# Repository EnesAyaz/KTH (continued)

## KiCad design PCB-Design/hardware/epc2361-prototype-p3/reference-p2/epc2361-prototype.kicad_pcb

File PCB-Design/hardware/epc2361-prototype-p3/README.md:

# P3 — left-side DC input and gate driver

This revision supersedes P2 for placement review. It is not released for manufacturing.

## Implemented arrangement

85 × 55 mm, four layers. DC+ and DC− M4 terminals are on the upper left, with auxiliary power and HI/LI inputs on the left edge. AC is on the right. LMG1210 is immediately left of the switch group. Both switch pairs face left toward the driver. There are two EPC2361s per switch, four total.

Twenty-four TDK C2012X7S2A105K125AB bus capacitors are fitted: six above and six below each local half bridge. All are on the top face. Upper banks C1–C6 and C19–C24 directly serve the short local commutation paths; lower banks C7–C12 and C25–C30 supplement DC-link decoupling through the collectors. The count was increased so the lower row does not require a long top-layer positive feeder to the high-side devices. Nominal total is 24 µF; effective capacitance at 75 V and permissible RMS ripple have not been established.

Every component has a silkscreen reference. Gate/source headers are marked G and S; the control header has individual 12V/GND/HI/GND/LI/GND labels. DC and AC terminals and all five test points are identified. The BOM contains all 51 purchased components; five additional footprints are copper test points.

## Four-layer allocation

| Layer | Actual baseline P3 use |
|---|---|
| L1 / F.Cu | Components, local DC+/AC/DC− power islands, local gate escapes and decoupling |
| L2 / In1.Cu | Continuous DC− plane underneath the power cells; no routed signals |
| L3 / In2.Cu | DC+ collector, with auxiliary/control and source-return routes |
| L4 / B.Cu | AC collector and gate-drive routes |

L1 is not a whole-board DC+ plane. The commutation current passes through separate positive, switch-node and negative regions. L2 provides a nearby opposing current path. L3/L4 are already used for power distribution as well as driver connections; they are not two unused signal layers.

The gate-routing candidate adds explicit star branches and source-return corridors on the lower layers. Consult its separate report for its actual result before adopting it. A gate route over an unrelated DC+ plane is not automatically a properly referenced gate loop.

## Proposed stackup for fabricator review

F.Cu 0.070 mm / dielectric 0.100 mm / In1.Cu 0.035 mm / core 1.190 mm / In2.Cu 0.035 mm / dielectric 0.100 mm / B.Cu 0.070 mm. Copper plus dielectric totals 1.600 mm, excluding masks. The 0.100 mm outer dielectric spacing is a requested finished value, not a confirmed catalogue stackup. Manufacturer tolerances and 0.15 mm routing at the chosen finished copper weight must be accepted before ordering. Finish and assembly stencil remain unspecified.

## Inductance interpretation

Both primary upper-bank local geometries now share the same 6 mm device spacing and 0.100 mm top-to-return dielectric. The P2 selected external finger estimate (~0.385 nH) and six-capacitor ideal component ESL (~0.080 nH) apply only to those selected local contributions. Their ~0.47 nH subtotal is not the complete loop or a measured value. Lower-bank vias, shared collectors, package contributions and coupling require extraction; do not divide component ESL by all 24 capacitors and call that the switching-loop ESL.

## Electrical and mechanical release items

Design targets remain 75 V maximum, 36.7 A RMS / 51.9 A peak total output, 50 kHz nominal and 100 kHz maximum. Current capability and thermal rise have not been validated. The gate-routing report must demonstrate acceptable branch symmetry and source-return topology; DRC alone cannot do this. Current distribution through collectors and vias, MLCC bias/ripple, bootstrap operating range and actual gate overshoot also remain engineering checks.

The controller supplies nonoverlapping HI/LI in independent-input mode; bootstrap startup/refresh is required. JCTRL1 is not isolated. Gate headers must not be driven by a second active driver while onboard outputs are connected. Individual 0 Ω gate-resistor footprints remain for tuning and isolation.

Cold plate, insulating TIM, clamping force, mechanical mounting and cable-lug support are not designed. Tall headers and capacitors constrain the plate underside. No fabrication-ready claim is made while these remain open. Exact EPC2361 and LMG1210 manufacturer models are still unavailable: their local 3D models are explicitly approximate envelopes. Generic header and capacitor models require manufacturer-dimension comparison.

## Project files

Open epc2361-prototype-p3.kicad_pro; open its PCB and press Alt+3 for 3D. BOM.md / BOM.json are the revised component lists. The schematic and PCB use local footprints and local visualization models. connectivity-check.txt checks exported net assignments and model presence; drc.rpt records baseline geometric checks. A separate gate candidate is not the baseline released design. P2 files copied into this folder during preparation are historical; use only the P3-named project for this revision.

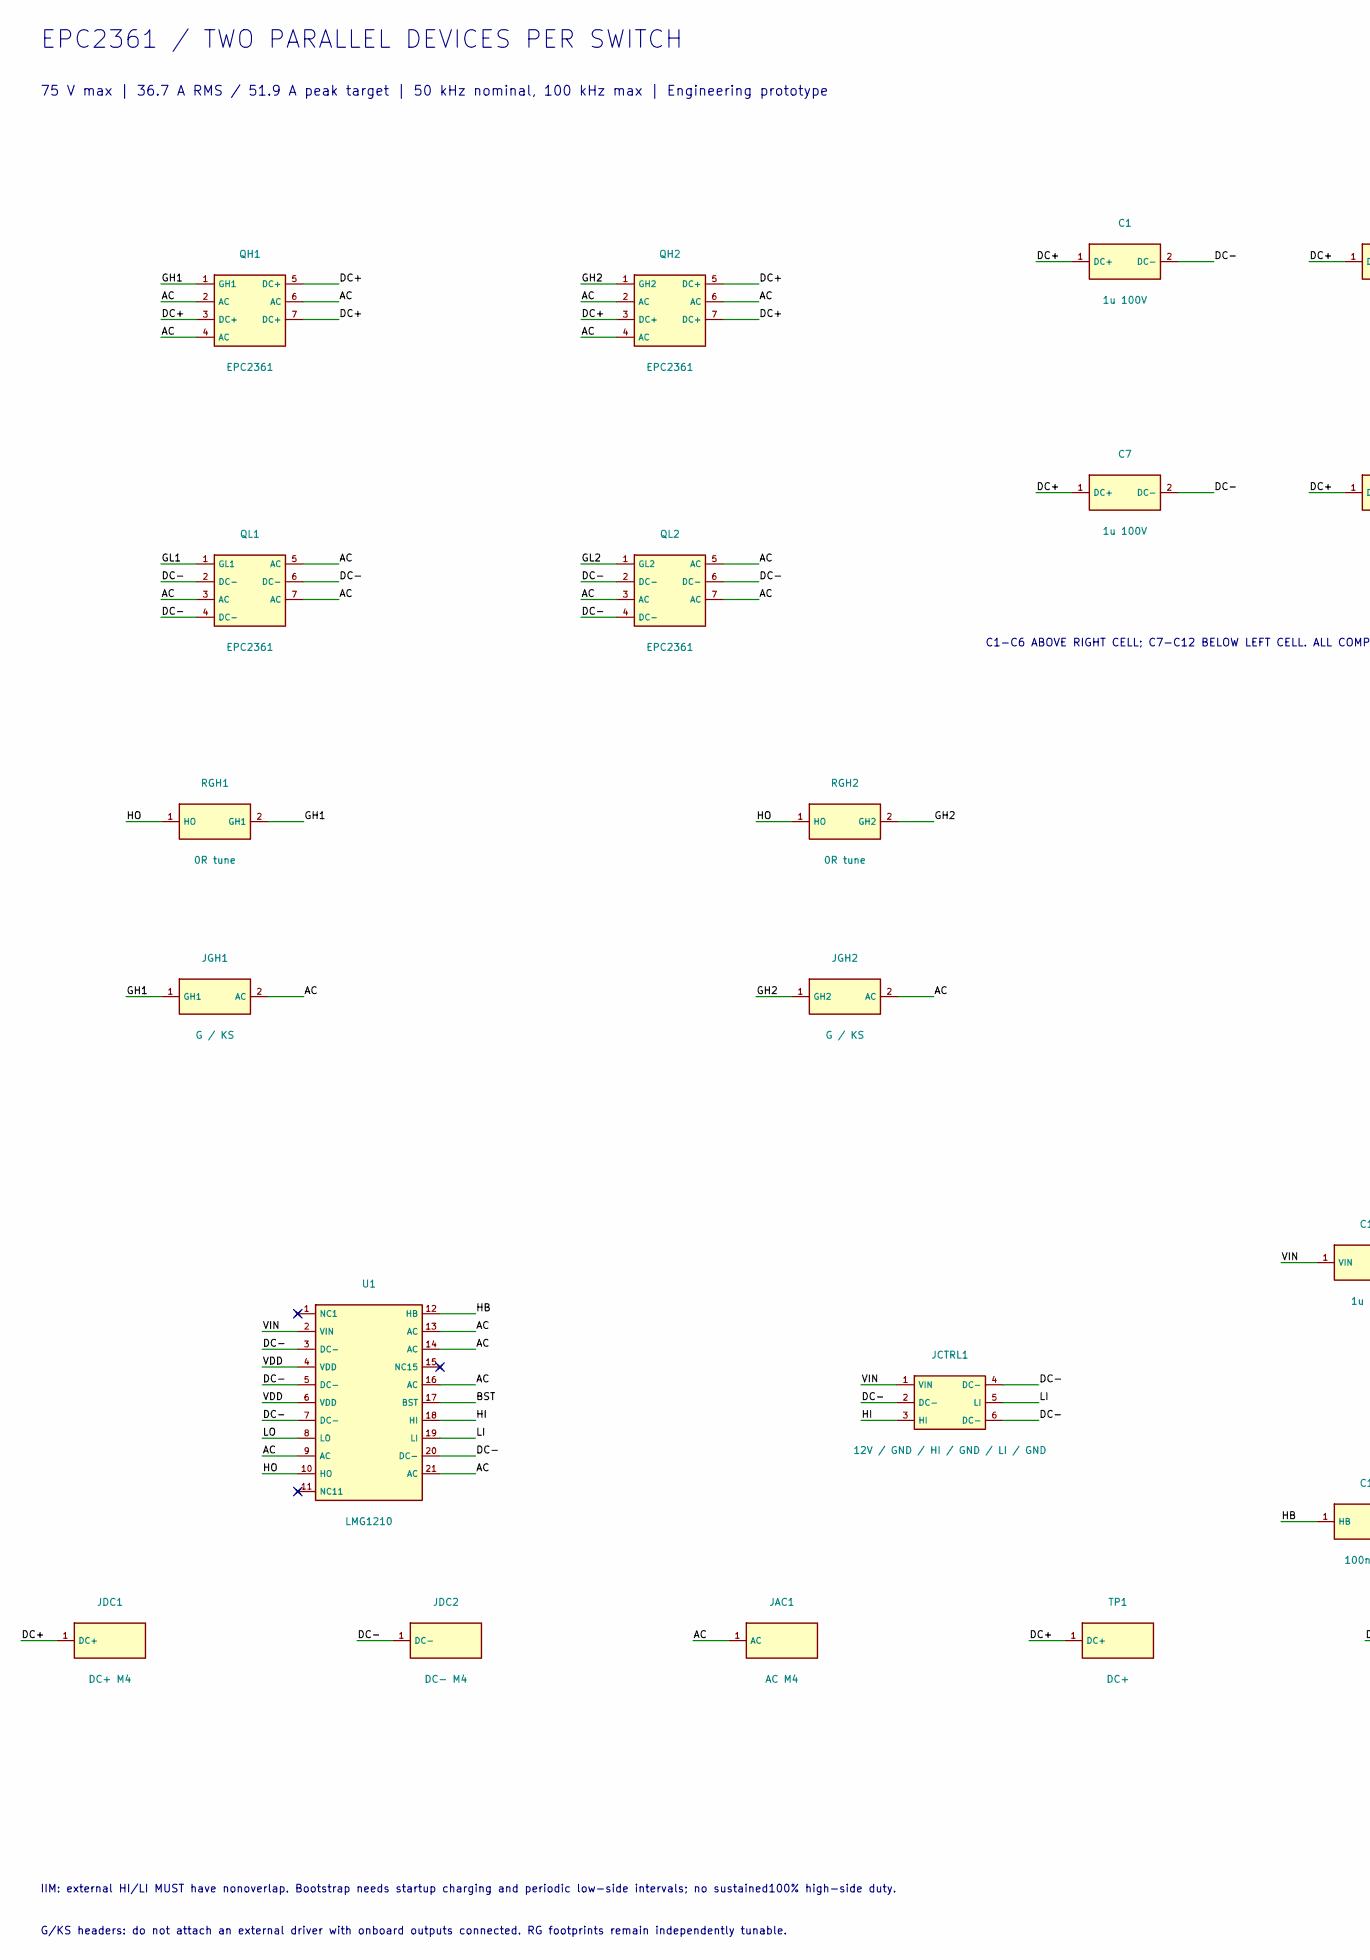
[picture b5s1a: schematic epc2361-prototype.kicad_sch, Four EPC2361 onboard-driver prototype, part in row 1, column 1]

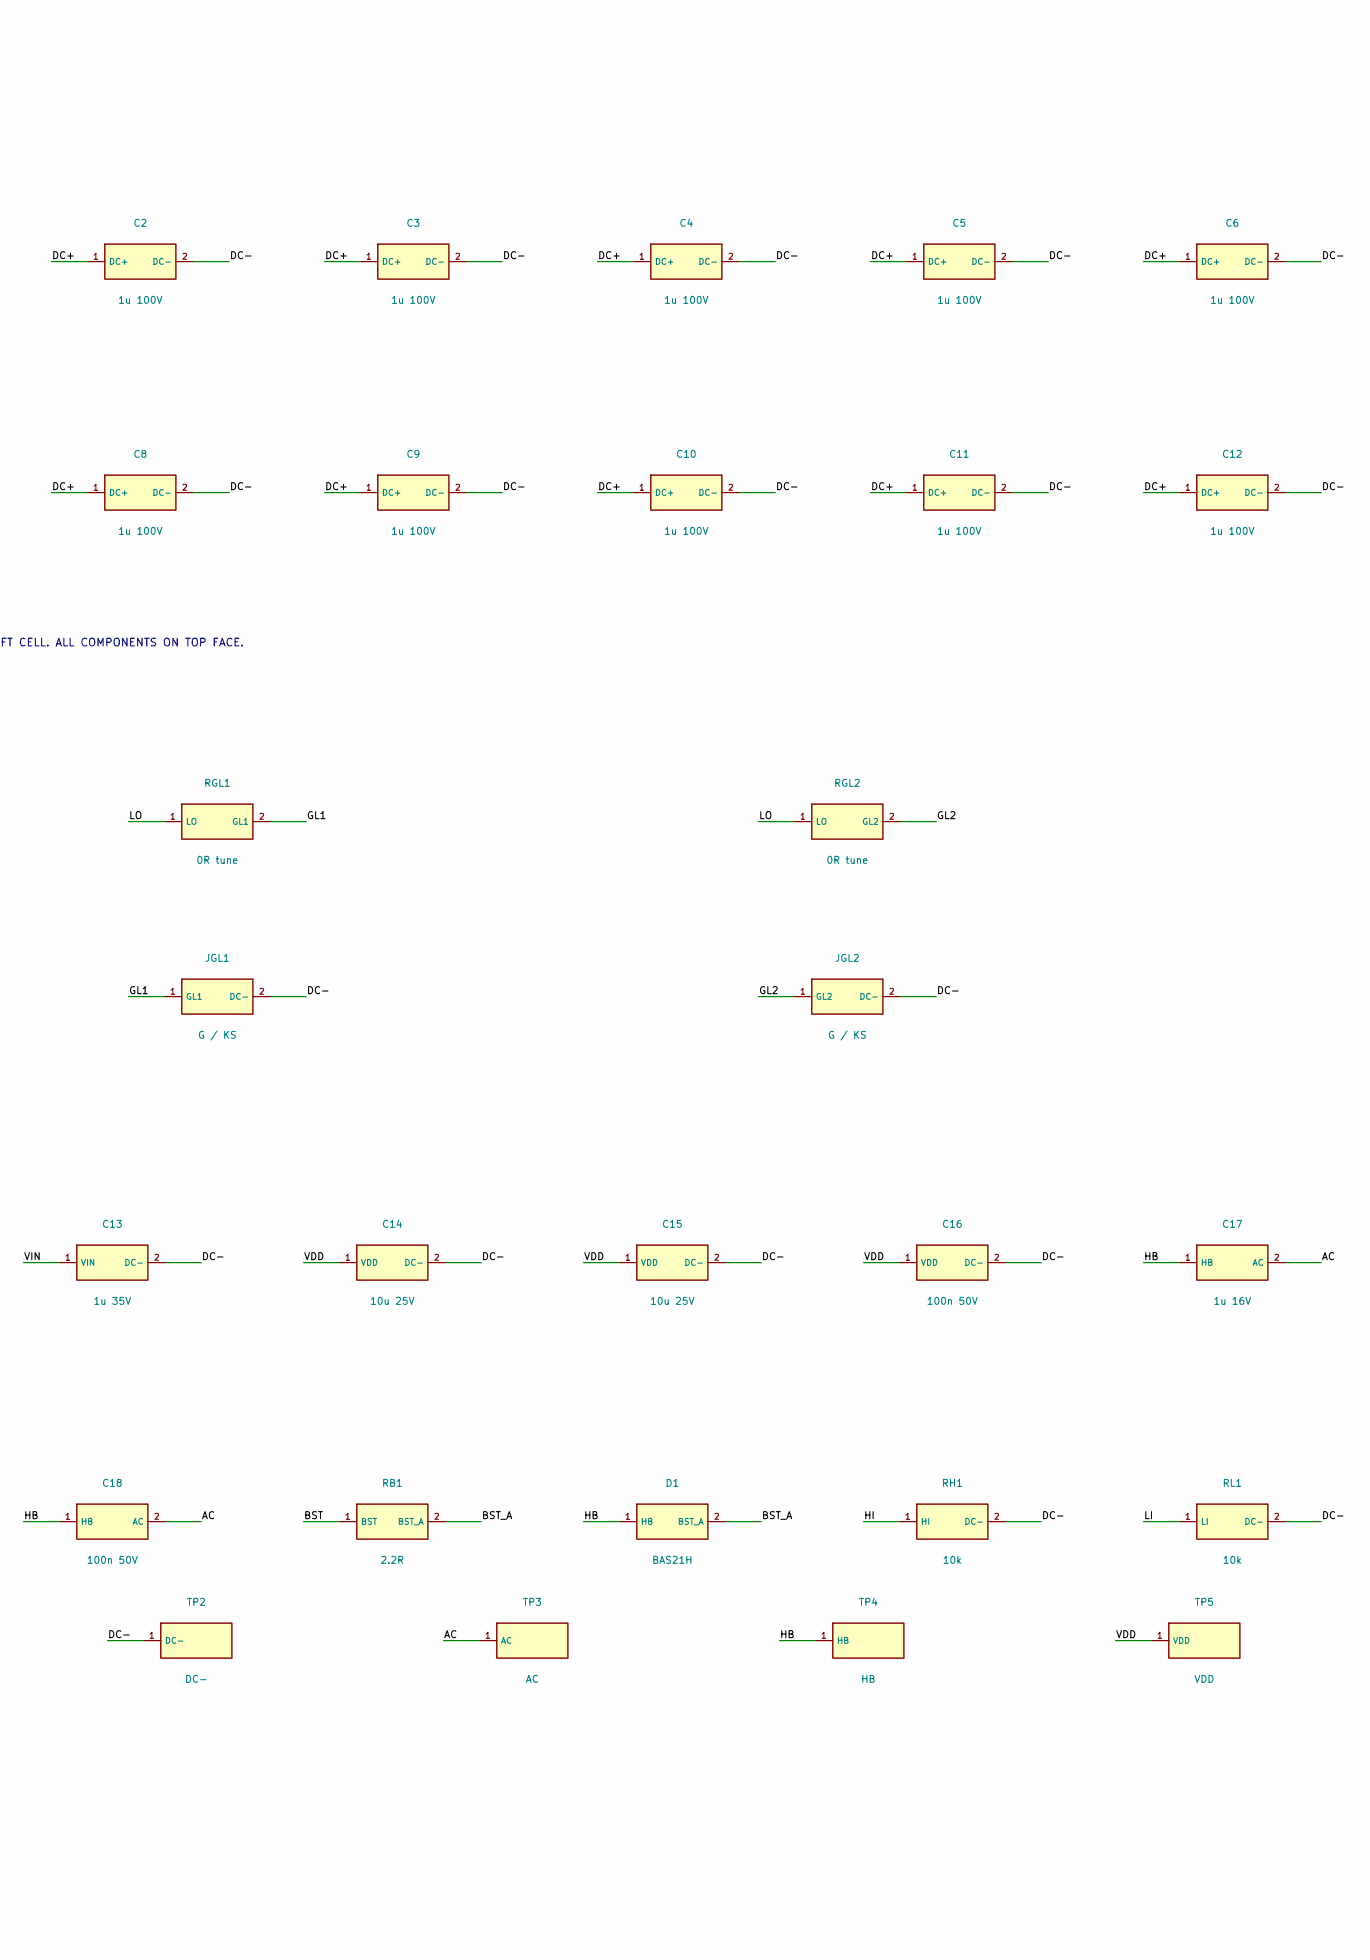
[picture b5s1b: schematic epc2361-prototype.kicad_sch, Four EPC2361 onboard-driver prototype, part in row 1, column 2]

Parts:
C1, C2, C3, C4, C5, C6, C7, C8, C9, C10, C11, C12: 1u 100V; C_0805_2012Metric
C13: 1u 35V; C_0603_1608Metric
C14, C15: 10u 25V; C_0805_2012Metric
C16, C18: 100n 50V; C_0603_1608Metric
C17: 1u 16V; C_0603_1608Metric
D1: BAS21H; D_SOD-123F
JAC1: AC M4; Wuerth_REDCUBE-THR_WP-THRBU_74650094_THR
JCTRL1: 12V / GND / HI / GND / LI / GND; PinHeader_1x06_P2.54mm_Vertical
JDC1: DC+ M4; Wuerth_REDCUBE-THR_WP-THRBU_74650094_THR
JDC2: DC- M4; Wuerth_REDCUBE-THR_WP-THRBU_74650094_THR
JGH1, JGH2: G / KS; PinHeader_1x02_P1.27mm_Vertical
JGL1, JGL2: G / KS; PinHeader_1x02_P1.27mm_Vertical
QH1, QH2: EPC2361
QL1, QL2: EPC2361
RB1: 2.2R; R_0603_1608Metric
RGH1, RGH2: 0R tune; R_0402_1005Metric
RGL1, RGL2: 0R tune; R_0402_1005Metric
RH1: 10k; R_0402_1005Metric
RL1: 10k; R_0402_1005Metric
TP1: DC+; Probe_Pad
TP2: DC-; Probe_Pad
TP3: AC; Probe_Pad
TP4: HB; Probe_Pad
TP5: VDD; Probe_Pad
U1: LMG1210; LMG1210_RVR

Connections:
AC: C17.2 (AC), C18.2 (AC), JAC1.1, JGH1.2 (AC), JGH2.2 (AC), QH1.2 (AC), QH1.4 (AC), QH1.6 (AC), QH2.2 (AC), QH2.4 (AC), QH2.6 (AC), QL1.3 (AC), QL1.5 (AC), QL1.7 (AC), QL2.3 (AC), QL2.5 (AC), QL2.7 (AC), TP3.1, U1.9 (AC), U1.13 (AC), U1.14 (AC), U1.16 (AC), U1.21 (AC)
BST: RB1.1 (BST), U1.17 (BST)
BST_A: D1.2 (BST_A), RB1.2 (BST_A)
DC+: C1.1 (DC+), C2.1 (DC+), C3.1 (DC+), C4.1 (DC+), C5.1 (DC+), C6.1 (DC+), C7.1 (DC+), C8.1 (DC+), C9.1 (DC+), C10.1 (DC+), C11.1 (DC+), C12.1 (DC+), JDC1.1, QH1.3 (DC+), QH1.5 (DC+), QH1.7 (DC+), QH2.3 (DC+), QH2.5 (DC+), QH2.7 (DC+), TP1.1
DC-: C1.2 (DC-), C2.2 (DC-), C3.2 (DC-), C4.2 (DC-), C5.2 (DC-), C6.2 (DC-), C7.2 (DC-), C8.2 (DC-), C9.2 (DC-), C10.2 (DC-), C11.2 (DC-), C12.2 (DC-), C13.2 (DC-), C14.2 (DC-), C15.2 (DC-), C16.2 (DC-), JCTRL1.2 (DC-), JCTRL1.4 (DC-), JCTRL1.6 (DC-), JDC2.1, JGL1.2 (DC-), JGL2.2 (DC-), QL1.2 (DC-), QL1.4 (DC-), QL1.6 (DC-), QL2.2 (DC-), QL2.4 (DC-), QL2.6 (DC-), RH1.2 (DC-), RL1.2 (DC-), TP2.1, U1.3 (DC-), U1.5 (DC-), U1.7 (DC-), U1.20 (DC-)
GH1: JGH1.1 (GH1), QH1.1 (GH1), RGH1.2 (GH1)
GH2: JGH2.1 (GH2), QH2.1 (GH2), RGH2.2 (GH2)
GL1: JGL1.1 (GL1), QL1.1 (GL1), RGL1.2 (GL1)
GL2: JGL2.1 (GL2), QL2.1 (GL2), RGL2.2 (GL2)
HB: C17.1 (HB), C18.1 (HB), D1.1 (HB), TP4.1, U1.12 (HB)
HI: JCTRL1.3 (HI), RH1.1 (HI), U1.18 (HI)
HO: RGH1.1 (HO), RGH2.1 (HO), U1.10 (HO)
LI: JCTRL1.5 (LI), RL1.1 (LI), U1.19 (LI)
LO: RGL1.1 (LO), RGL2.1 (LO), U1.8 (LO)
NC1: U1.1 (NC1)
NC11: U1.11 (NC11)
NC15: U1.15 (NC15)
VDD: C14.1 (VDD), C15.1 (VDD), C16.1 (VDD), TP5.1, U1.4 (VDD), U1.6 (VDD)
VIN: C13.1 (VIN), JCTRL1.1 (VIN), U1.2 (VIN)

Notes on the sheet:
EPC2361 / TWO PARALLEL DEVICES PER SWITCH
75 V max | 36.7 A RMS / 51.9 A peak target | 50 kHz nominal, 100 kHz max | Engineering prototype
C1-C6 ABOVE RIGHT CELL; C7-C12 BELOW LEFT CELL. ALL COMPONENTS ON TOP FACE.
IIM: external HI/LI MUST have nonoverlap. Bootstrap needs startup charging and periodic low-side intervals; no sustained100% high-side duty.
G/KS headers: do not attach an external driver with onboard outputs connected. RG footprints remain independently tunable.

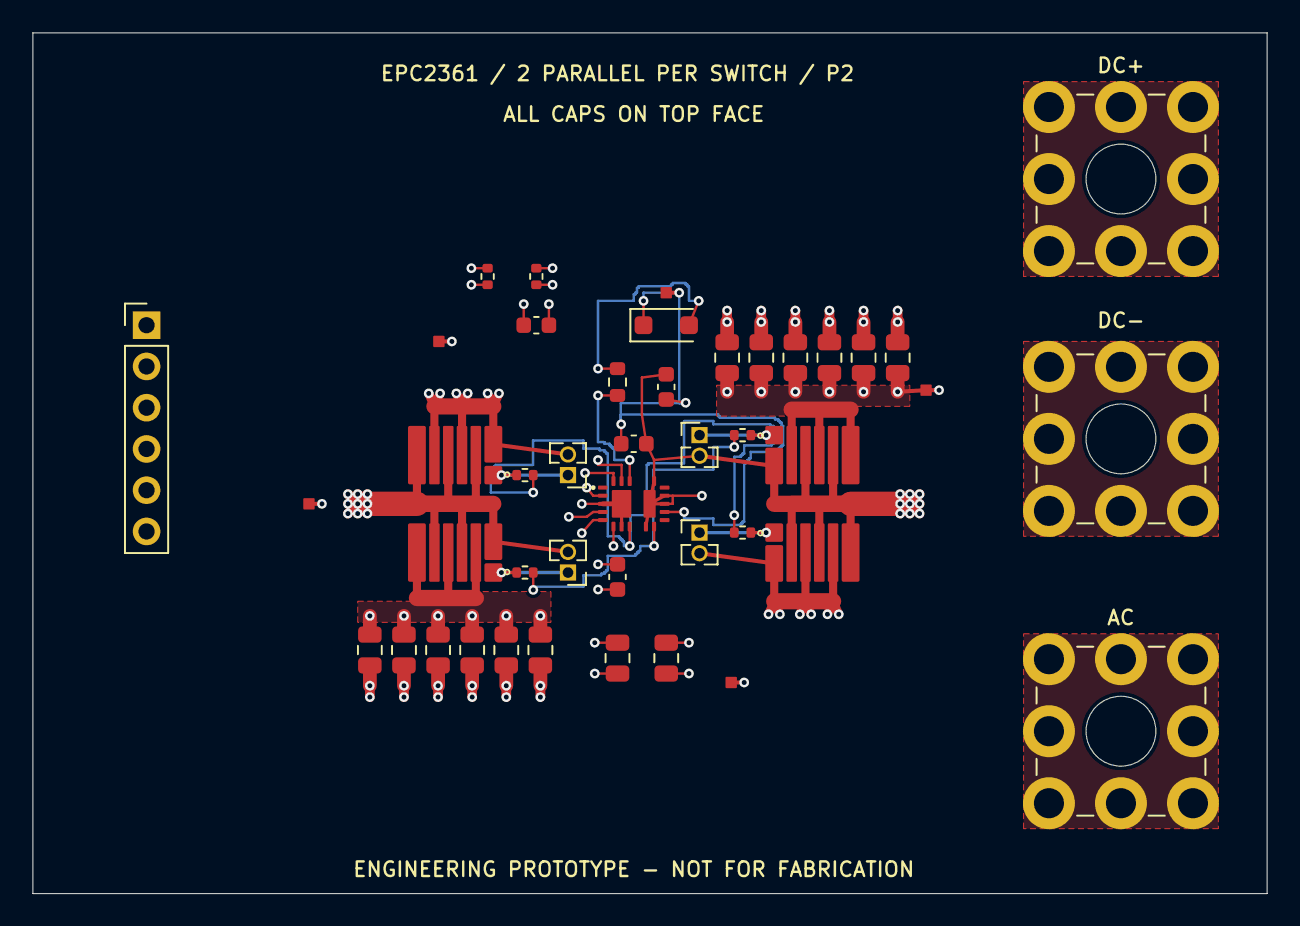
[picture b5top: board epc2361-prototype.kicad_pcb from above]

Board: 4 copper layers, 76.0 x 53.0 mm, 44 parts (0 on the bottom side), 16 nets.

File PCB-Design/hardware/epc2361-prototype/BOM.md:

# Prototype BOM

All quantities are for one four-FET board. Provisional engineering BOM; not purchasing release.

| References | Qty | MPN | Value | Footprint | Fit | Notes |
|---|---:|---|---|---|---|---|
| QH1, QL1, QH2, QL2 | 4 | EPC2361 | EPC2361 | epc2361-prototype:EPC2361 | Fit |  |
| C1, C2, C3, C4, C5, C6, C7, C8, C9, C10, C11, C12 | 12 | C2012X7S2A105K125AB | 1u 100V | Capacitor_SMD:C_0805_2012Metric | Fit |  |
| RGH1, RGL1, RGH2, RGL2 | 4 | RC0402JR-070RL | 0R tune | Resistor_SMD:R_0402_1005Metric | Fit | Individual gate damping footprint. Tune during double-pulse testing. |
| JGH1, JGL1, JGH2, JGL2 | 4 | FTS-102-01-L-S | G / KS | Connector_PinHeader_1.27mm:PinHeader_1x02_P1.27mm_Vertical | Fit | Measurement/external-drive header; never connect a second active driver. Remove local series resistor to isolate onboard output. Generic footprint: verify manufacturer drawing before release. |
| JDC1 | 1 | 74650094 | DC+ M4 | TerminalBlock_Wuerth:Wuerth_REDCUBE-THR_WP-THRBU_74650094_THR | Fit | 85 A maximum at20C is terminal-only; assembly/current path requires validation. 1.2Nm maximum specified torque. |
| JDC2 | 1 | 74650094 | DC- M4 | TerminalBlock_Wuerth:Wuerth_REDCUBE-THR_WP-THRBU_74650094_THR | Fit | 85 A maximum at20C is terminal-only; assembly/current path requires validation. 1.2Nm maximum specified torque. |
| JAC1 | 1 | 74650094 | AC M4 | TerminalBlock_Wuerth:Wuerth_REDCUBE-THR_WP-THRBU_74650094_THR | Fit | 85 A maximum at20C is terminal-only; assembly/current path requires validation. 1.2Nm maximum specified torque. |
| U1 | 1 | LMG1210RVRR | LMG1210 | epc2361-prototype:LMG1210_RVR | Fit | IIM: external nonoverlapping HI/LI; no internal shoot-through interlock in this mode. |
| JCTRL1 | 1 | TSW-106-07-G-S | 12V / GND / HI / GND / LI / GND | Connector_PinHeader_2.54mm:PinHeader_1x06_P2.54mm_Vertical | Fit |  |
| C13 | 1 | C1608X7R1V105K080AC | 1u 35V | Capacitor_SMD:C_0603_1608Metric | Fit | Verify effective capacitance and temperature; VDD X5R parts rated85C. |
| C14, C15 | 2 | C2012X5R1E106K125AB | 10u 25V | Capacitor_SMD:C_0805_2012Metric | Fit | Verify effective capacitance and temperature; VDD X5R parts rated85C. |
| C16, C18 | 2 | C1608X7R1H104K080AA | 100n 50V | Capacitor_SMD:C_0603_1608Metric | Fit | Verify effective capacitance and temperature; VDD X5R parts rated85C. |
| C17 | 1 | C1608X7R1C105K080AC | 1u 16V | Capacitor_SMD:C_0603_1608Metric | Fit | Verify effective capacitance and temperature; VDD X5R parts rated85C. |
| RB1 | 1 | RC0603FR-072R2L | 2.2R | Resistor_SMD:R_0603_1608Metric | Fit |  |
| D1 | 1 | BAS21H,115 | BAS21H | Diode_SMD:D_SOD-123F | Fit | External bootstrap diode: cathode HB, anode BST_A. Not a bootstrap voltage clamp. |
| RH1, RL1 | 2 | RC0402FR-0710KL | 10k | Resistor_SMD:R_0402_1005Metric | Fit |  |
| TP1 | 1 | PCB copper test pad | DC+ | epc2361-prototype:Probe_Pad | Fit | PCB feature; no purchased component. |
| TP2 | 1 | PCB copper test pad | DC- | epc2361-prototype:Probe_Pad | Fit | PCB feature; no purchased component. |
| TP3 | 1 | PCB copper test pad | AC | epc2361-prototype:Probe_Pad | Fit | PCB feature; no purchased component. |
| TP4 | 1 | PCB copper test pad | HB | epc2361-prototype:Probe_Pad | Fit | PCB feature; no purchased component. |
| TP5 | 1 | PCB copper test pad | VDD | epc2361-prototype:Probe_Pad | Fit | PCB feature; no purchased component. |

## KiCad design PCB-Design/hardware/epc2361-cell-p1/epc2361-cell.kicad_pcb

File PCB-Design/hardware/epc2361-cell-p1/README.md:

# P1: EPC-style one-pair power-loop layout

This is the revised native KiCad 7 project requested from EPC's optimal-loop illustration. The original P0 project is preserved in the sibling directory. Open `epc2361-cell.kicad_pro` here.

## What changed

- 27 x 30 mm study outline. One high-side EPC2361 at (15,16) mm and one low-side at (15,22) mm; 6 mm pitch.
- Six 0805 capacitors across the top above the high-side device, with positive terminals facing the devices. Broad top DC+ copper replaces the long side rail.
- Capacitor negative terminals connect through paired vias to the first inner DC- layer. Low-side source vias complete the return directly beneath the top power path.
- Six optional/DNP bottom capacitors sit underneath the top bank. Their rail transitions are outside the device lands. The DC+ via antipads perforate L2 locally but leave a continuous return; their effect needs extraction. Bottom parts are not assumed equally effective at high frequencies.
- No driver IC. Individual top G/Kelvin-source contact pairs, series gate-resistor sites and optional local gate-source resistors remain.
- All power ports and seven probe pads are routed. Pads are interface placeholders, not selected or rated power sockets. Probe mapping: TP1 GH, TP2 high-side source/AC, TP3 GL, TP4 low-side source/DC-, TP5 DC+, TP6 DC-, TP7 AC.
- Insulated top cold-plate contact corridor reserved over the FET pair. Full plate, TIM, mounting and clamping remain mechanical design work.

## Capacitors

C1-C6: TDK C2012X7S2A105K125AB, 1 uF / 100 V / X7S / 0805, six populated provisionally. C7-C12 use the same part but are DNP until impedance and heating justify population. Nominal capacitance is 6 uF top-only or 12 uF with both banks; neither number is the retained capacitance at 75 V.

TDK's simple equivalent-circuit model gives 0.480 nH for this component. The six-capacitor ideal uncoupled component-only result is 0.080 nH. This excludes mounting, shared copper, vias, FET interconnections and coupling, and is not the complete loop inductance. The 1210 alternative has 0.600 nH model inductance and more nominal capacitance. These are conventional MLCCs selected for a low-inductance assembled bank; no suitable 100 V reverse-geometry part was verified.

See `../../docs/capacitor-selection-p1.md` for manufacturer links, alternatives and qualification limits. C at 75 V and capacitor RMS heating remain unqualified. External bulk capacitance is still required.

## Proposed stackup

The board file records a provisional four-layer stack: 70 um top copper, 100 um prepreg to the 35 um L2 return, 1.19 mm core, 35 um L3, 100 um prepreg, and 70 um bottom copper. Copper plus dielectric totals 1.60 mm before solder mask. FR4 electrical properties are placeholders, not a selected laminate. Fabricator confirmation is required. L3 currently has no functional plane; layer count alone does not reduce the loop.

The key optimization parameter is the 0.10 mm top-to-L2 separation. A parallel-plate estimate must use the actual overlapping current corridor and include transitions separately. No extracted or measured inductance is claimed.

## Checks and release status

30 components and 60 pin assignments match the KiCad-exported schematic netlist and PCB. Native PCB DRC: zero violations, zero unconnected pads, zero footprint errors. Native schematic ERC has not been run. Views: `top.svg`, `return.svg`, `bottom.svg`; PNG previews alongside them. Bottom export is viewed through the board from above unless mirrored in KiCad.

This is a routed engineering study, not a manufacturing release or a demonstrated 36.7 A RMS cell rating. Wide power distribution, terminal ratings, assembly footprint sign-off, capacitor derating, coupled parasitic extraction, switching tests and electrothermal validation are outstanding. The six-parallel module and gate-driver PCB are deferred.

## Rebuild

Run `scripts/build_cell_p1.py` with KiCad Python. Set `CELL_REVISION=epc2361-cell-p1`, run `scripts/build_cell_schematic.py`, export the XML netlist to this folder, then run `scripts/check_cell.py` with the same environment variable. The audit fills zones and writes the DRC report. Preserve manual edits before regenerating.

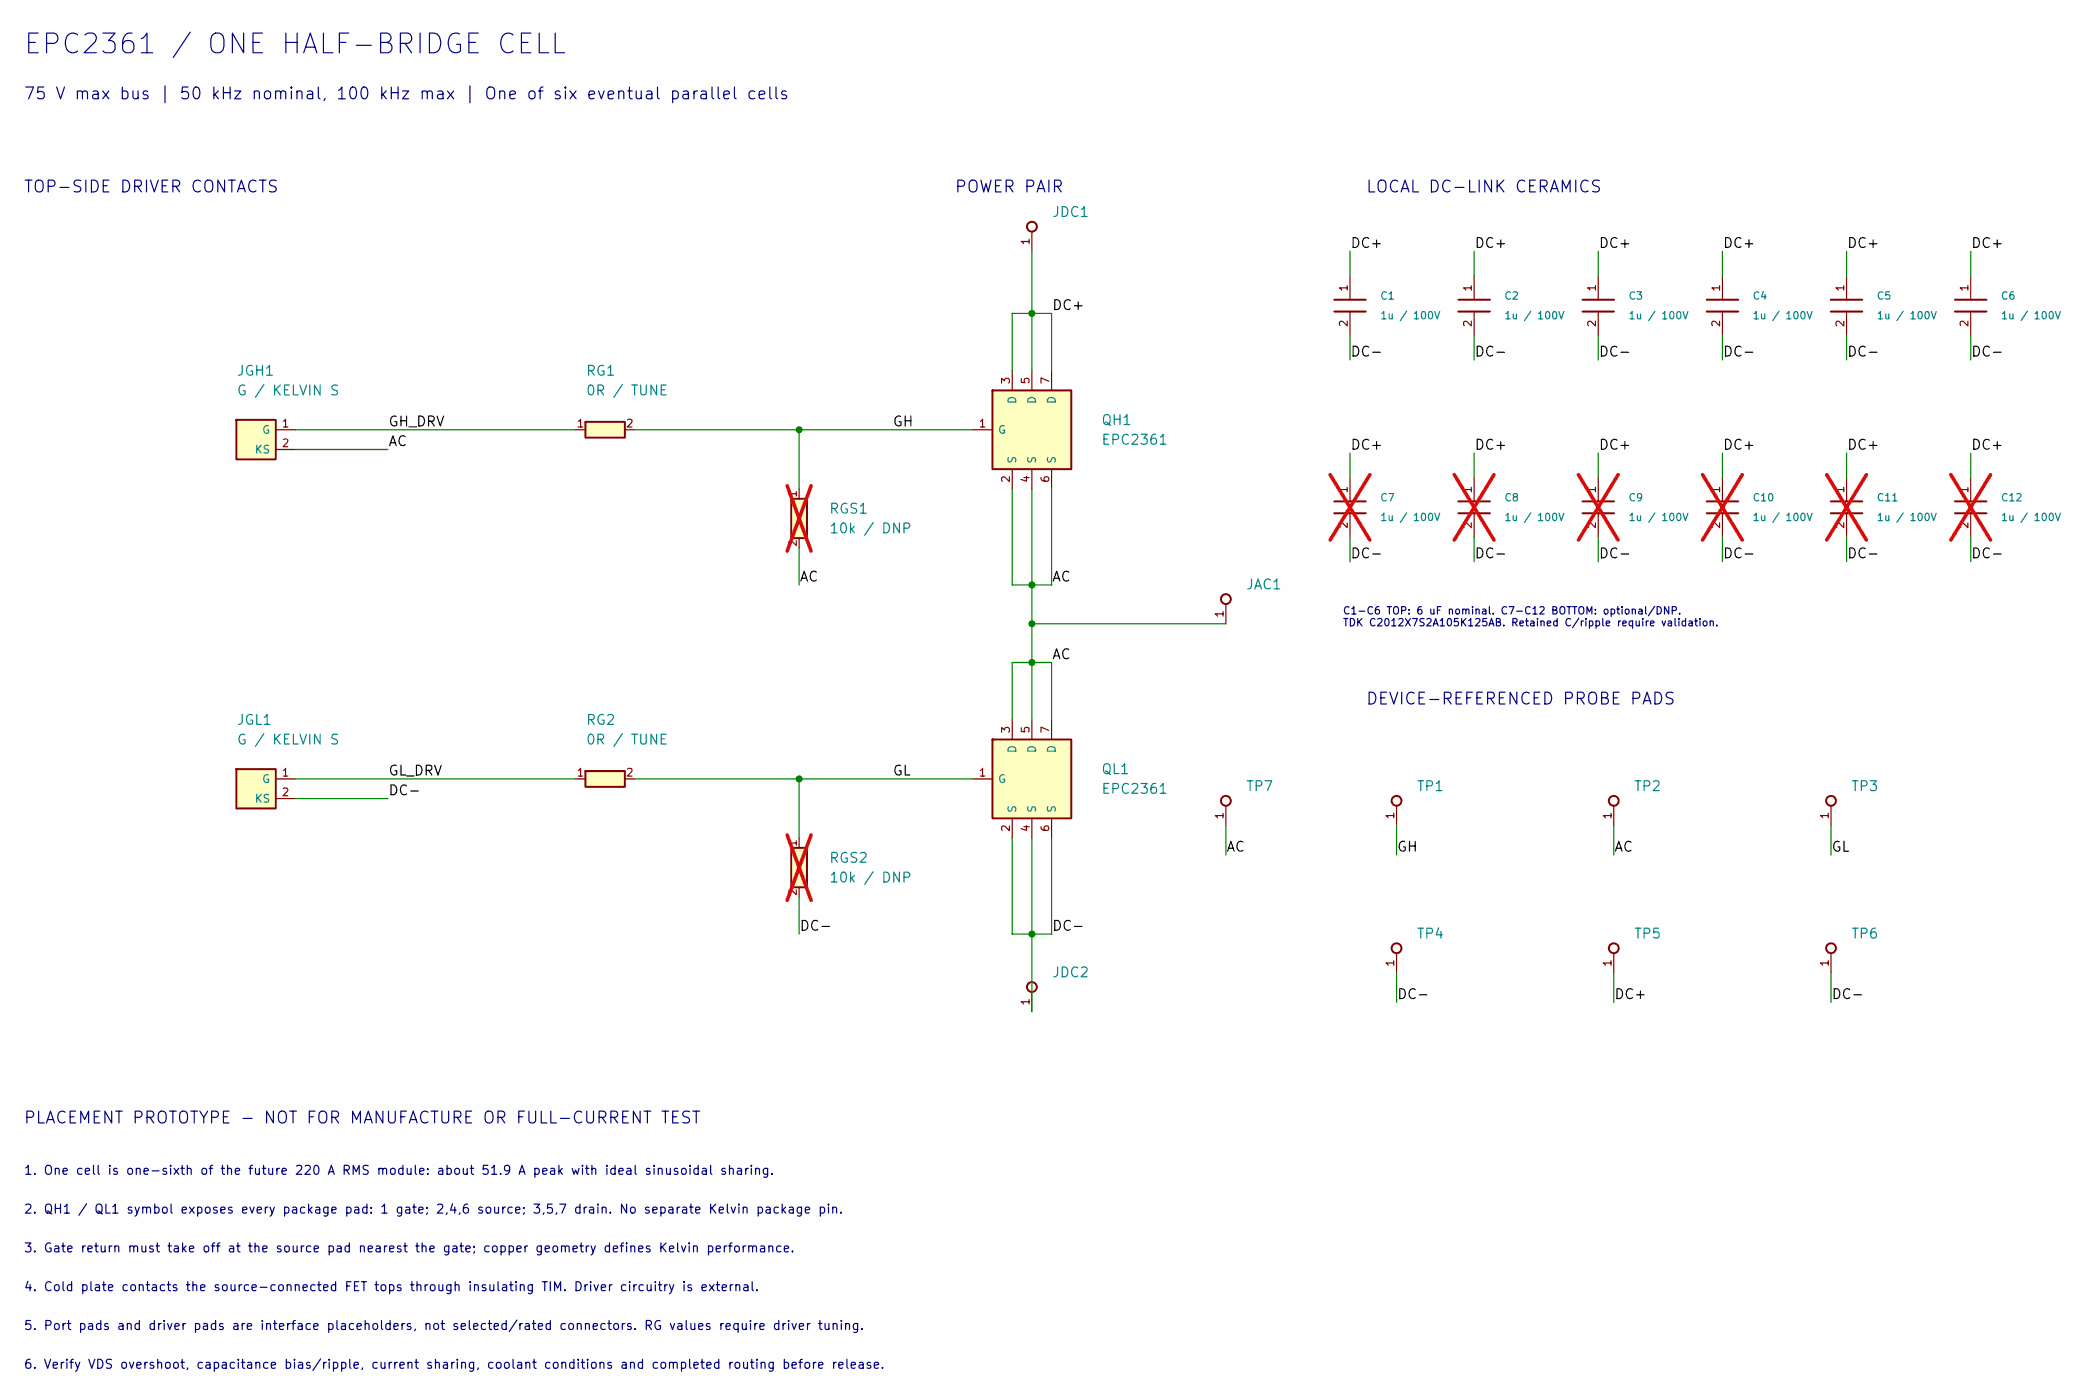
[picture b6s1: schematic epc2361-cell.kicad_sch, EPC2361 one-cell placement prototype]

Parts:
C1, C2, C3, C4, C5, C6: 1u / 100V; C_0805_2012Metric
C7, C8, C9, C10, C11, C12: 1u / 100V; C_0805_2012Metric; not fitted
JAC1: AC PORT PAD; Power_Port_Pad
JDC1: DC+ PORT PAD; Power_Port_Pad
JDC2: DC- PORT PAD; Power_Port_Pad
JGH1: G / KELVIN S; Gate_Source_Pads
JGL1: G / KELVIN S; Gate_Source_Pads
QH1: EPC2361
QL1: EPC2361
RG1, RG2: 0R / TUNE; R_0402_1005Metric
RGS1, RGS2: 10k / DNP; R_0402_1005Metric; not fitted
TP1: GH; Probe_Pad
TP2, TP7: AC; Probe_Pad
TP3: GL; Probe_Pad
TP4, TP6: DC-; Probe_Pad
TP5: DC+; Probe_Pad

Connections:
AC: JAC1.1, JGH1.2 (KS), QH1.2 (S), QH1.4 (S), QH1.6 (S), QL1.3 (D), QL1.5 (D), QL1.7 (D), RGS1.2, TP2.1, TP7.1
DC+: C1.1, C2.1, C3.1, C4.1, C5.1, C6.1, C7.1, C8.1, C9.1, C10.1, C11.1, C12.1, JDC1.1, QH1.3 (D), QH1.5 (D), QH1.7 (D), TP5.1
DC-: C1.2, C2.2, C3.2, C4.2, C5.2, C6.2, C7.2, C8.2, C9.2, C10.2, C11.2, C12.2, JDC2.1, JGL1.2 (KS), QL1.2 (S), QL1.4 (S), QL1.6 (S), RGS2.2, TP4.1, TP6.1
GH: QH1.1 (G), RG1.2, RGS1.1, TP1.1
GH_DRV: JGH1.1 (G), RG1.1
GL: QL1.1 (G), RG2.2, RGS2.1, TP3.1
GL_DRV: JGL1.1 (G), RG2.1

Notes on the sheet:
EPC2361 / ONE HALF-BRIDGE CELL
75 V max bus | 50 kHz nominal, 100 kHz max | One of six eventual parallel cells
TOP-SIDE DRIVER CONTACTS
POWER PAIR
LOCAL DC-LINK CERAMICS
C1-C6 TOP: 6 uF nominal. C7-C12 BOTTOM: optional/DNP. TDK C2012X7S2A105K125AB. Retained C/ripple require validation.
DEVICE-REFERENCED PROBE PADS
PLACEMENT PROTOTYPE - NOT FOR MANUFACTURE OR FULL-CURRENT TEST
1. One cell is one-sixth of the future 220 A RMS module: about 51.9 A peak with ideal sinusoidal sharing.
2. QH1 / QL1 symbol exposes every package pad: 1 gate; 2,4,6 source; 3,5,7 drain. No separate Kelvin package pin.
3. Gate return must take off at the source pad nearest the gate; copper geometry defines Kelvin performance.
4. Cold plate contacts the source-connected FET tops through insulating TIM. Driver circuitry is external.
5. Port pads and driver pads are interface placeholders, not selected/rated connectors. RG values require driver tuning.
6. Verify VDS overshoot, capacitance bias/ripple, current sharing, coolant conditions and completed routing before release.

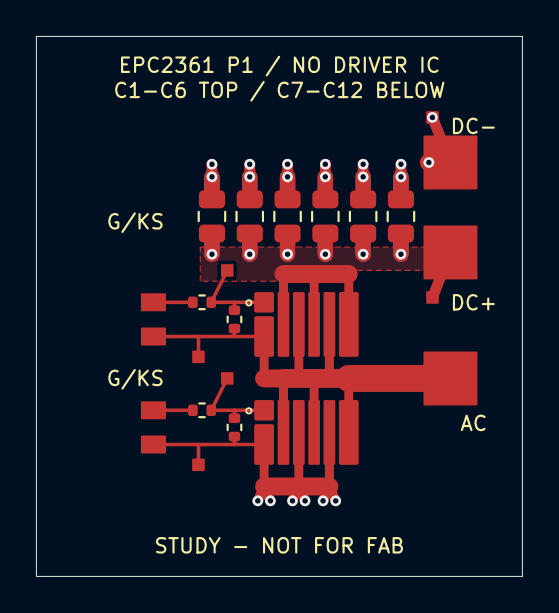
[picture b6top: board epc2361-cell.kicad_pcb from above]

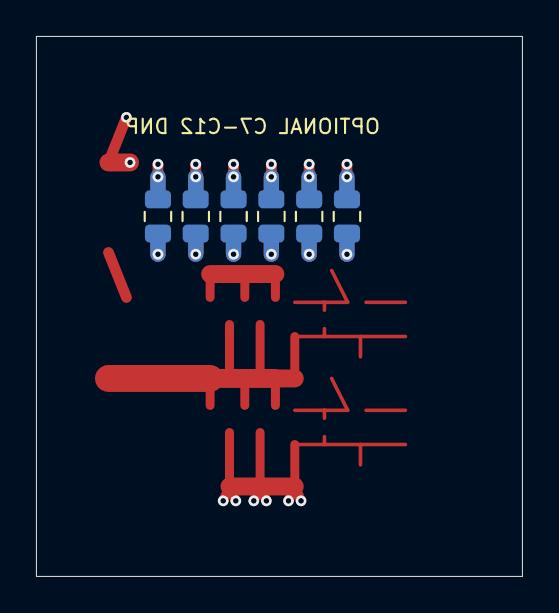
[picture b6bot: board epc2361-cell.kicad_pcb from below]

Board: 4 copper layers, 27.0 x 30.0 mm, 30 parts (6 on the bottom side), 7 nets.

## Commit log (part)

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2023-03-22 I will update this repo weekly with a report.
2023-04-24 I create a iterative loss analysis for only conduction losses
2023-04-24 switching loss is added
2023-04-25 established structs and generalized the script
2023-05-17 a new start
2023-05-30 weekly reports
    small literature review for bearing current is made
2023-05-31 updating the presentations
2023-06-02 weekly report about mitigation of bearing current
2023-06-05 Weekly reports are combined in Stepwise Design
2023-06-05 online carrier phase shift calculation to reduce the CMV
2023-06-05 for loop is created to calculate the phase requirements
2023-06-06 phases are calculated, it is a "paper" idea !!!
2023-06-06 updated version
2023-06-07 the presentation and analytic switching loop are updated
2023-06-07 presentation update
2023-06-08 create comparative analysis
2023-06-12 comparative analysis are added
2023-06-13 comparative analysis
2023-06-15 conduction losses and switching losses
2023-06-18 Hemizero presentation
2023-07-04 new common mode reduction method
    matlab model is created, a presentation is created
2023-07-04 loss calculations, for 2L and 3L converters
2023-07-18 dv/dt
2023-07-18 updated presentation
2023-08-29 weekly reports
2023-09-14 inmotion presentation
2023-09-14 inductance desing
2023-09-14 savings
2023-09-18 adding presentations
2023-10-04 gitignore
2023-11-16 loss calculation
2023-11-16 inductance
2023-11-16 modulation
2024-04-21 Drive cycle analysis
2024-04-21 loss calculation models
2024-04-21 ECCE paper draft and first submission
2024-04-21 weekly reports updates
2024-04-21 update 2
2024-04-21 Imperix
2024-08-07 capacitor sizing
2024-08-07 ecce
2024-08-07 harmonic loss modelling
2024-08-07 simulink models
2024-08-07 loss calculations
2024-08-07 common mode voltage model
2024-08-07 presentations and specs
2024-08-21 simulink three phase
2024-09-06 weekly reports update
2024-10-01 access paper documents, first files
2024-10-25 presentation of the meeting updates
2024-10-25 specs copyright
2024-10-25 access paper about CMV
2024-11-06 articles
2024-11-06 airgap harmonics
2024-11-06 IEMDC paper
    IEMDC paper- 2level calculations are written. In my SPEC paper, I found miscalculation in rds_on. We should come back to it later.
2024-11-07 weekly reports
    weekly reports about PWM generation and current waveforms with switching ripple
2024-11-11 Airgap harmonics and some technical documents
    airgap harmonics, first proposal are done. TI initialization and PCB documents are added.
2024-11-15 Update .gitignore
    ansys results file are ignored
2024-11-15 Update airgap harmonics.pptx
    airgap harmonic utilization- first idea
2024-11-15 Ansys models for DC-link impedance model
2024-11-15 .cir files from ansys
    netlist of impedance matrix, including resistances and inductances
2024-11-15 Ltspice model for Dc link modelling
2024-11-15 matlab files for DC-link modelling
    We should think about the resonant structure, and should we try operating a frequency give the uneven current distribution
2024-11-26 Ltspice files for DC bus and gitignore
2024-11-26 data, parasitic circuits for 3 phase
2024-11-26 matlab to get the response for SPWM of 3 phase
2024-11-26 ansys model and reports etc
2024-11-26 weekly report for harmonic modelling
2024-12-18 weekly reports on harmonic model of the inverter
2025-01-03 draft version of BOM for the first prototype
2025-02-14 ECCE-2024 update
2025-02-14 ECCE-2025 first files and IEMDC the codes for final submission
2025-02-23 ECCE 2025 and Access Paper
2025-02-24 ECCE-2025 Experimental figures
2025-02-26 2Level code for current waveforms and gitignore for mat, raw and log files
2025-02-26 three level simulations
2025-02-26 gitignore zip files
2025-02-28 Back2back inverter with Wolfspeed Model, gate drivers
2025-03-05 IEMDC-2025 waveforms updated and checked FFT
2025-03-05 Updating BOM of first prototype
2025-03-05 B2B inverter and three phase inverter LTSpice model
2025-03-10 presentation about scania visit
2025-03-10 Ttype modulation
2025-03-11 2 level and 3 level losses for IEMDC
2025-03-19 back2back inverter simulink model
    Ttype modulation SVPWM
2025-03-24 back-to-back
2025-03-25 hemizero meeting
2025-04-04 B2B inductor design
2025-04-04 Prototyping BOM and presentations
2025-04-04 git ignore
2025-04-04 ACCESS paper, simulations and imperix code. Inductance and capacitance values will be selected.
2025-04-22 gitignores and presentations
2025-04-22 experimental figures osciloscope for CMV journal paper
2025-04-22 experimental raw data codes for CMV journal
2025-04-22 imperix codes
2025-04-22 raw data- CMV journal
2025-04-22 ignore the raw data
2025-04-23 experimental figures were updated, and finalized the paper and cover letter
2025-04-23 update gitignore for raw data
2025-05-19 Capacitor DC-link current minimization
2025-05-19 ECCE-2025- simulations
2025-05-19 Prototyping
2025-05-20 ECCE2025 and bearing current model
2025-07-10 ECCE-2025
2025-07-10 Bearing current and misc
2025-07-18 capacitor-sizing journal, drawings for intro and modulation
2025-07-18 prototyping single phase inverter
2025-07-29 capacitor sizing ripple minimization
2025-08-12 capacitor sizing- LUT
2025-10-08 field excitation, transition gift
2025-10-08 harmonic loss modeling paper started
2025-10-08 protoyping control three phase is created
2025-10-08 CMV paper FFT results
2025-10-14 multiphaseproductsEV and CMV paper simulink
2025-10-30 1.2kV access paper codes and several updates
2025-11-07 1.2kV journal paper files
2025-12-15 1.2kV Paper Graphs
2025-12-15 Update gitignore
2025-12-15 Staff Meeting and 50 Percent meeting
2025-12-15 Colorimetric Setup
2026-01-23 new drawings for 1.2kV Paper
2026-02-09 Auxliary power supply elimination
2026-03-30 auxliary power module elimination
2026-04-29 1.2kV submission
2026-04-29 OPT field excitation
2026-04-29 miscellaneous
2026-05-18 mitigation of CMV - OJPEL files
2026-05-18 IPEC 2026 Poster
2026-05-18 loss calculations harmonics
